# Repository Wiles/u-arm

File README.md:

# u-arm
PCB for Linux on 8bit http://dmitry.gr/?r=05.Projects&amp;proj=07.%20Linux%20on%208bit

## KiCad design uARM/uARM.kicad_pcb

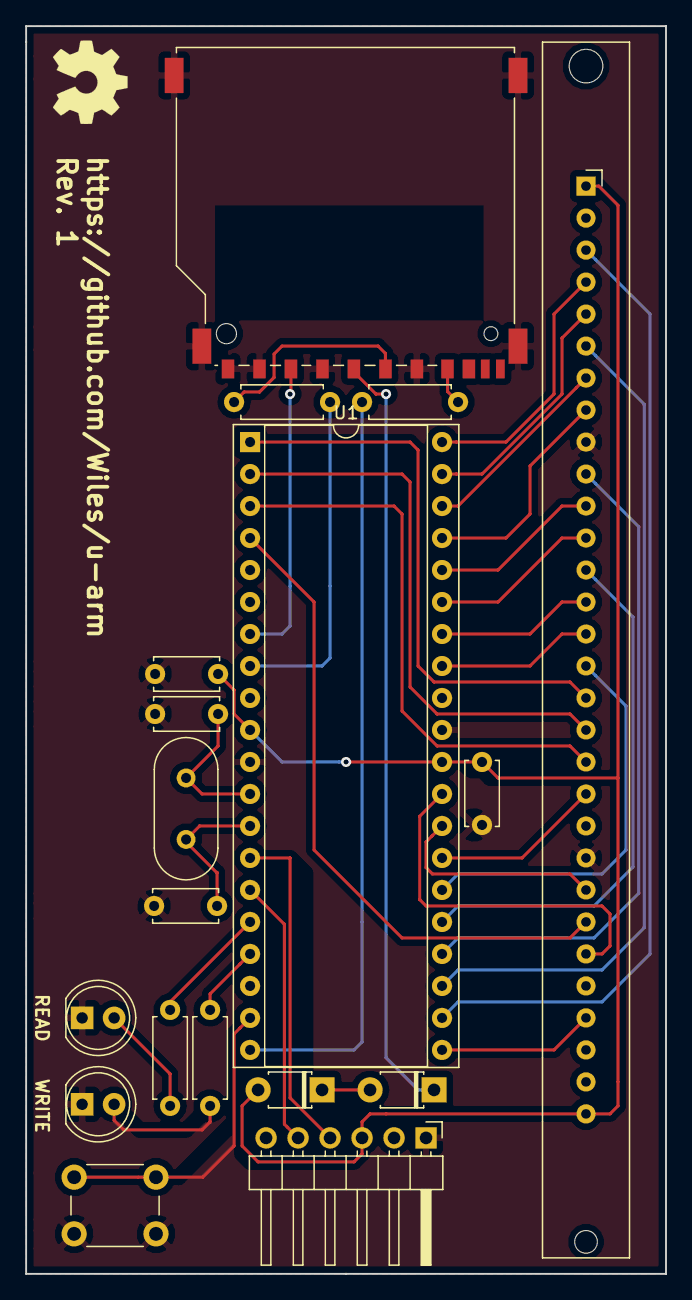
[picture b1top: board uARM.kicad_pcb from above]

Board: 2 copper layers, 50.8 x 99.1 mm, 18 parts (0 on the bottom side), 39 nets.

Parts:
C1, C2: C_Small; C_Disc_D5.0mm_W2.5mm_P5.00mm
C3, C4: .1u; C_Disc_D5.0mm_W2.5mm_P5.00mm
D1, D2: LED; LED_D5.0mm
D3, D4: D_Small; D_T-1_P5.08mm_Horizontal
J1: Micro_SD_Card; SD_TE_2041021
J2: FTDI; PinHeader_1x06_P2.54mm_Horizontal
R1, R2, R3, R4: 1k; R_Axial_DIN0207_L6.3mm_D2.5mm_P7.62mm_Horizontal
SW1: SW_Push; SW_PUSH_6mm
U1: ATmega1284P-PU; DIP-40_W15.24mm_Socket
U2: SIMM
Y1: Crystal; Crystal_HC49-U_Vertical

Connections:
+3V3: D3.1, J1.4
+5V: C3.1, C4.1, D4.2, J2.3, U1.10, U1.30, U2.1, U2.30
/A0: U1.40, U2.4
/A1: U1.39, U2.5
/A2: U1.38, U2.7
/A3: U1.37, U2.8
/A4: U1.36, U2.11
/A5: U1.35, U2.12
/A6: U1.34, U2.14
/A7: U1.33, U2.15
/A8: U1.1, U2.17
/A9: U1.2, U2.18
/A10: U1.3, U2.19
/A11: U1.4, U2.24
/D0: U1.22, U2.3
/D1: U1.23, U2.6
/D2: U1.24, U2.10
/D3: U1.25, U2.13
/D4: U1.26, U2.16
/D5: U1.27, U2.20
/D6: U1.28, U2.23
/D7: U1.29, U2.25
BTN: SW1.2, U1.19
GND: C1.1, C2.2, C3.2, C4.2, D1.1, D2.1, J1.1, J1.3, J1.6, J1.9, J1.12, J2.1, SW1.1, U1.11, U1.31, U2.9, U2.22
MISO: R1.2, U1.20
MOSI: J1.2, U1.7
unnamed: C1.2, U1.13, Y1.2
unnamed: C2.1, U1.12, Y1.1
unnamed: D1.2, R4.1
unnamed: D2.2, R3.2
unnamed: D3.2, D4.1
unnamed: J1.5, R2.2
unnamed: J1.7, R1.1
RAS: U1.21, U2.27
READ: R3.1, U1.16
RX: J2.4, U1.14
SCK: R2.1, U1.8
TX: J2.5, U1.15
WRITE: R4.2, U1.17

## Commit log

2018-08-21 Added FTDI header
2018-08-29 SIMM footprint and Rev. 1 PCB
2021-04-18 Fixed reference to symbol library
